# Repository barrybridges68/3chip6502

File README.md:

# 3chip6502
6502,6532 very simple single board computer

Built as a curiousity. Can be used with NMOS cpus or the new WDC 65c02.

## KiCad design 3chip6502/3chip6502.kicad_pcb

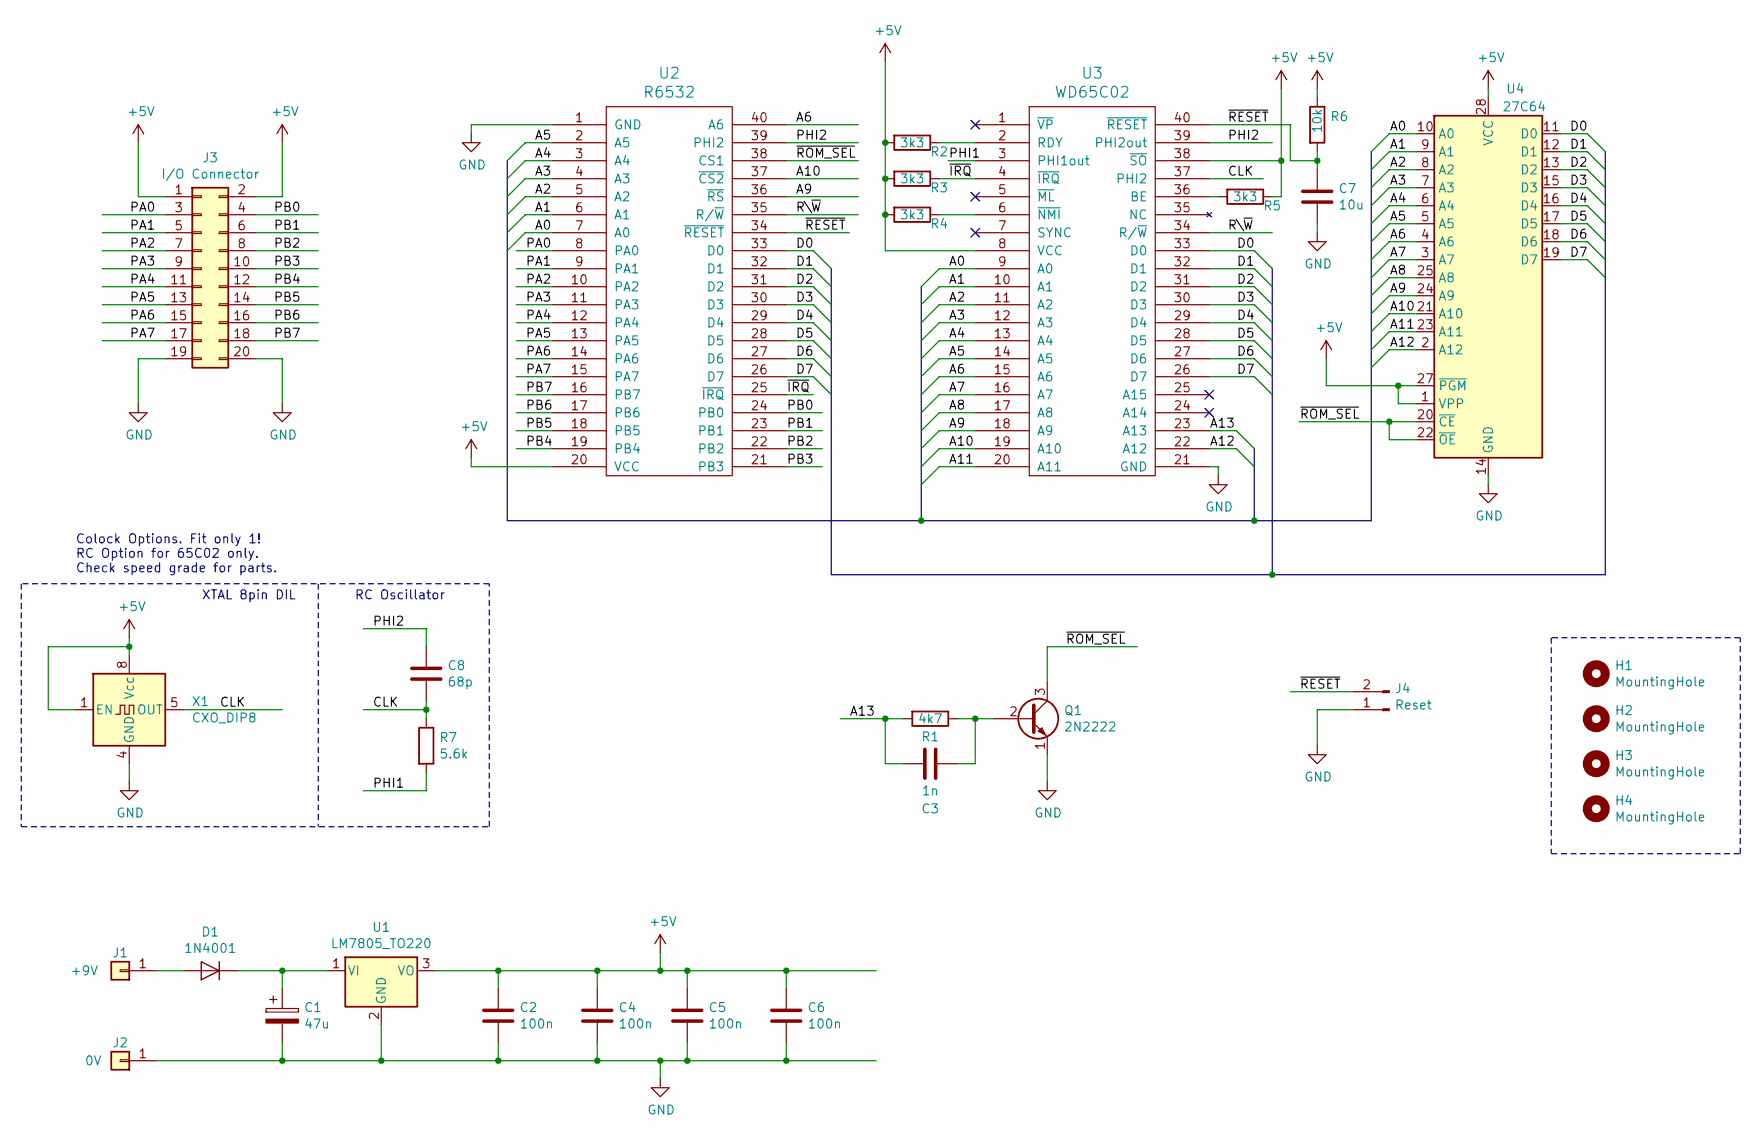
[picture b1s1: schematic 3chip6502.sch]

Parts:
C1: 47u; CP_Radial_D5.0mm_P2.50mm
C2, C4, C5, C6: 100n; C_Disc_D4.3mm_W1.9mm_P5.00mm
C3: 1n; C_Disc_D4.3mm_W1.9mm_P5.00mm
C7: 10u; CP_Radial_D5.0mm_P2.50mm
C8: 68p; C_Disc_D3.0mm_W2.0mm_P2.50mm
D1: 1N4001; D_A-405_P5.08mm_Vertical_KathodeUp
H1, H2, H3, H4: MountingHole; MountingHole_3.2mm_M3_ISO14580_Pad
J1: +9V; Pin_D1.0mm_L10.0mm
J2: 0V; Pin_D1.0mm_L10.0mm
J3: I/O Connector; Pin_Header_Straight_2x10_Pitch2.54mm
J4: Reset; Pin_Header_Straight_1x02_Pitch2.54mm
Q1: 2N2222; TO-92_Inline_Narrow_Oval
R1: 4k7; R_Axial_DIN0207_L6.3mm_D2.5mm_P10.16mm_Horizontal
R2, R3, R4, R5: 3k3; R_Axial_DIN0207_L6.3mm_D2.5mm_P10.16mm_Horizontal
R6: 10k; R_Axial_DIN0207_L6.3mm_D2.5mm_P10.16mm_Horizontal
R7: 5.6k; R_Axial_DIN0207_L6.3mm_D2.5mm_P10.16mm_Horizontal
U1: LM7805_TO220; TO-220-3_Vertical
U2: R6532; DIP-40_W15.24mm_Socket
U3: WD65C02; DIP-40_W15.24mm_Socket
U4: 27C64; DIP-28_W15.24mm
X1: CXO_DIP8; Oscillator_DIP-8

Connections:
+5V: C2.1, C4.1, C5.1, C6.1, J3.1, J3.2, R2.2, R3.2, R4.2, R5.1, R6.1, U1.3 (VO), U2.20 (VCC), U3.8 (VCC), U3.38 (~SO), U4.1 (VPP), U4.27 (~PGM), U4.28 (VCC), X1.1 (EN), X1.8 (Vcc)
/A0: U2.7 (A0), U3.9 (A0), U4.10 (A0)
/A1: U2.6 (A1), U3.10 (A1), U4.9 (A1)
/A2: U2.5 (A2), U3.11 (A2), U4.8 (A2)
/A3: U2.4 (A3), U3.12 (A3), U4.7 (A3)
/A4: U2.3 (A4), U3.13 (A4), U4.6 (A4)
/A5: U2.2 (A5), U3.14 (A5), U4.5 (A5)
/A6: U2.40 (A6), U3.15 (A6), U4.4 (A6)
/A7: U3.16 (A7), U4.3 (A7)
/A8: U3.17 (A8), U4.25 (A8)
/A9: U2.36 (~RS), U3.18 (A9), U4.24 (A9)
/A10: U2.37 (~CS2), U3.19 (A10), U4.21 (A10)
/A11: U3.20 (A11), U4.23 (A11)
/A12: U3.22 (A12), U4.2 (A12)
/A13: C3.1, R1.2, U3.23 (A13)
/CLK: C8.2, R7.1, U3.37 (PHI2), X1.5 (OUT)
/D0: U2.33 (D0), U3.33 (D0), U4.11 (D0)
/D1: U2.32 (D1), U3.32 (D1), U4.12 (D1)
/D2: U2.31 (D2), U3.31 (D2), U4.13 (D2)
/D3: U2.30 (D3), U3.30 (D3), U4.15 (D3)
/D4: U2.29 (D4), U3.29 (D4), U4.16 (D4)
/D5: U2.28 (D5), U3.28 (D5), U4.17 (D5)
/D6: U2.27 (D6), U3.27 (D6), U4.18 (D6)
/D7: U2.26 (D7), U3.26 (D7), U4.19 (D7)
/PA0: J3.3, U2.8 (PA0)
/PA1: J3.5, U2.9 (PA1)
/PA2: J3.7, U2.10 (PA2)
/PA3: J3.9, U2.11 (PA3)
/PA4: J3.11, U2.12 (PA4)
/PA5: J3.13, U2.13 (PA5)
/PA6: J3.15, U2.14 (PA6)
/PA7: J3.17, U2.15 (PA7)
/PB0: J3.4, U2.24 (PB0)
/PB1: J3.6, U2.23 (PB1)
/PB2: J3.8, U2.22 (PB2)
/PB3: J3.10, U2.21 (PB3)
/PB4: J3.12, U2.19 (PB4)
/PB5: J3.14, U2.18 (PB5)
/PB6: J3.16, U2.17 (PB6)
/PB7: J3.18, U2.16 (PB7)
/PHI1: R7.2, U3.3 (PHI1out)
/PHI2: C8.1, U2.39 (PHI2), U3.39 (PHI2out)
/R\~W: U2.35 (R/~W), U3.34 (R/~W)
/~IRQ: R3.1, U2.25 (~IRQ), U3.4 (~IRQ)
/~RESET: C7.1, J4.2, R6.2, U2.34 (~RESET), U3.40 (~RESET)
/~ROM_SEL: Q1.3 (C), U2.38 (CS1), U4.20 (~CE), U4.22 (~OE)
GND: C1.2, C2.2, C4.2, C5.2, C6.2, C7.2, J2.1, J3.19, J3.20, J4.1, Q1.1 (E), U1.2 (GND), U2.1 (GND), U3.21 (GND), U4.14 (GND), X1.4 (GND)
unnamed: C1.1, D1.1 (K), U1.1 (VI)
unnamed: C3.2, Q1.2 (B), R1.1
unnamed: D1.2 (A), J1.1
unnamed: R2.1, U3.2 (RDY)
unnamed: R4.1, U3.6 (~NMI)
unnamed: R5.2, U3.36 (BE)

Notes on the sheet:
XTAL 8pin DIL
RC Oscillator
Colock Options. Fit only 1! RC Option for 65C02 only. Check speed grade for parts.

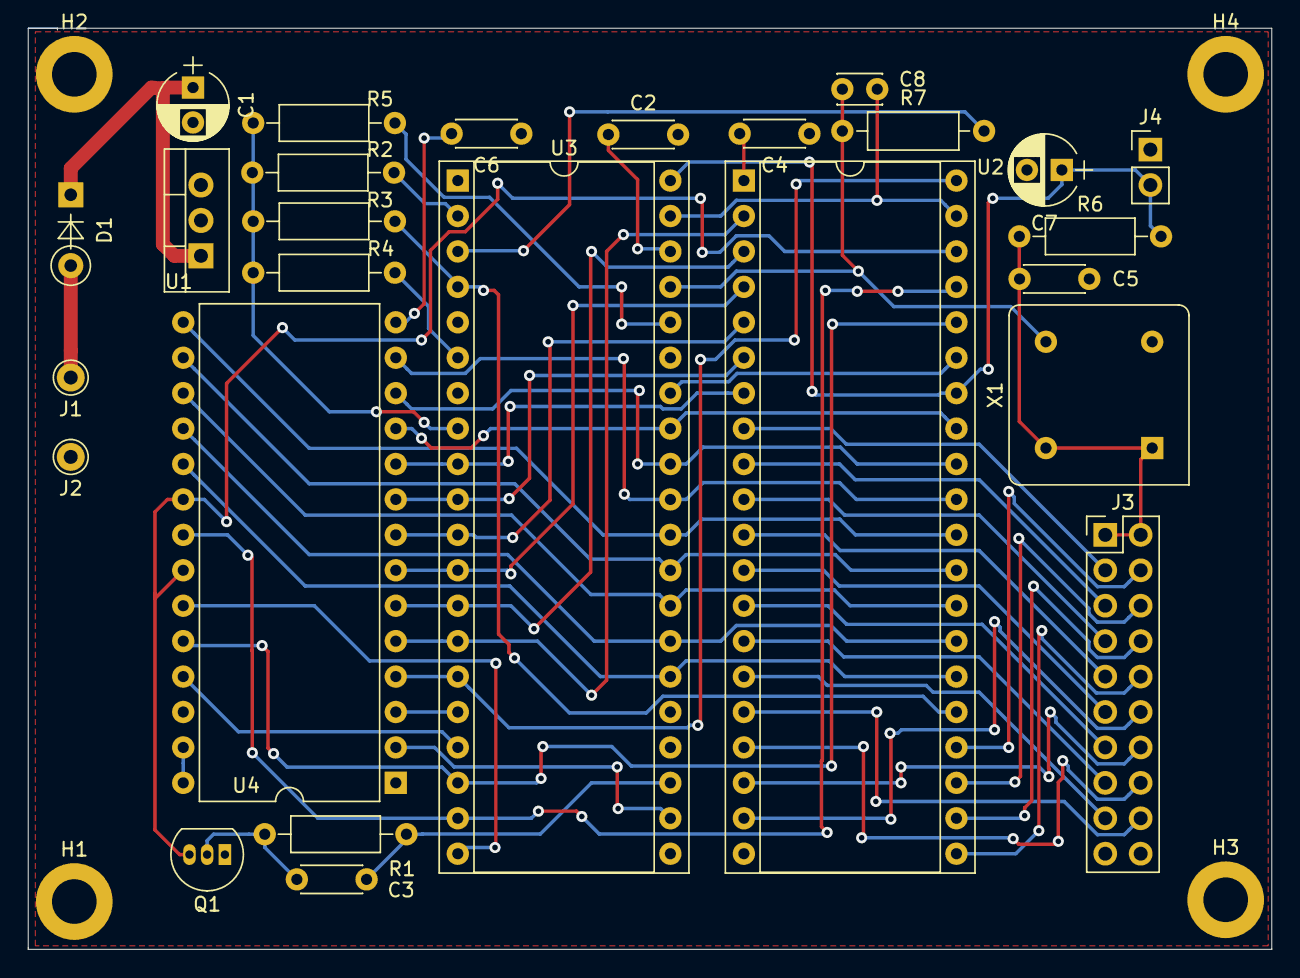
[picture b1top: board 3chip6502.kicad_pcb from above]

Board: 2 copper layers, 89.2 x 66.0 mm, 30 parts (0 on the bottom side), 53 nets.

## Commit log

2020-07-27 Initial commit.
